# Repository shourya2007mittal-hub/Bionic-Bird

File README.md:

# Bionic-Bird

I made a bionic butterfly based on a custom ESP32 Board that holds an IMU and a Barometer for control. Is has 2 Servos each servos control a Wing. It uses a 3.7V battery and one can control it through your phone via bluetooth.

## Features

- Base on ESP32 Module
- Has IMU (MPU_6050)
- Has a Barometer (BMP280)
- Uses 2 High torque Servoes
- Would have LED strips on the wings

## Components BOM

| Item | Quantity | Price (USD) | Source |
|------|------------|------------|---------|
| PCBA | - | $129.29 | JLCPCB |
| PCB Shipping | - | $11.99 | JLCPCB |
| High Torque Servo | 2 | $22.04 (for 2) | https://robu.in/product/waveshare-2-3kg-dual-axis-serial-bus-servo/ |
| LED Strip | 1 | $3.82 | https://robu.in/product/5m-neon-light-dance-party-decor-light-neon-led-lamp-flexible-el-wire-rope-tube-waterproof-led-strip-only-el-wire-yellow/ |

## Cost Summary

| Item | Cost (USD) |
|------|------------|
| PCBA | $129.29 |
| PCB Shipping | $11.99 |
| High Torque Servo (2 units) | $22.04 |
| LED Strip | $3.82 |

**Total Estimated Cost:** **$167.14**

### Schematic

###  PCB Design

### 3D Design

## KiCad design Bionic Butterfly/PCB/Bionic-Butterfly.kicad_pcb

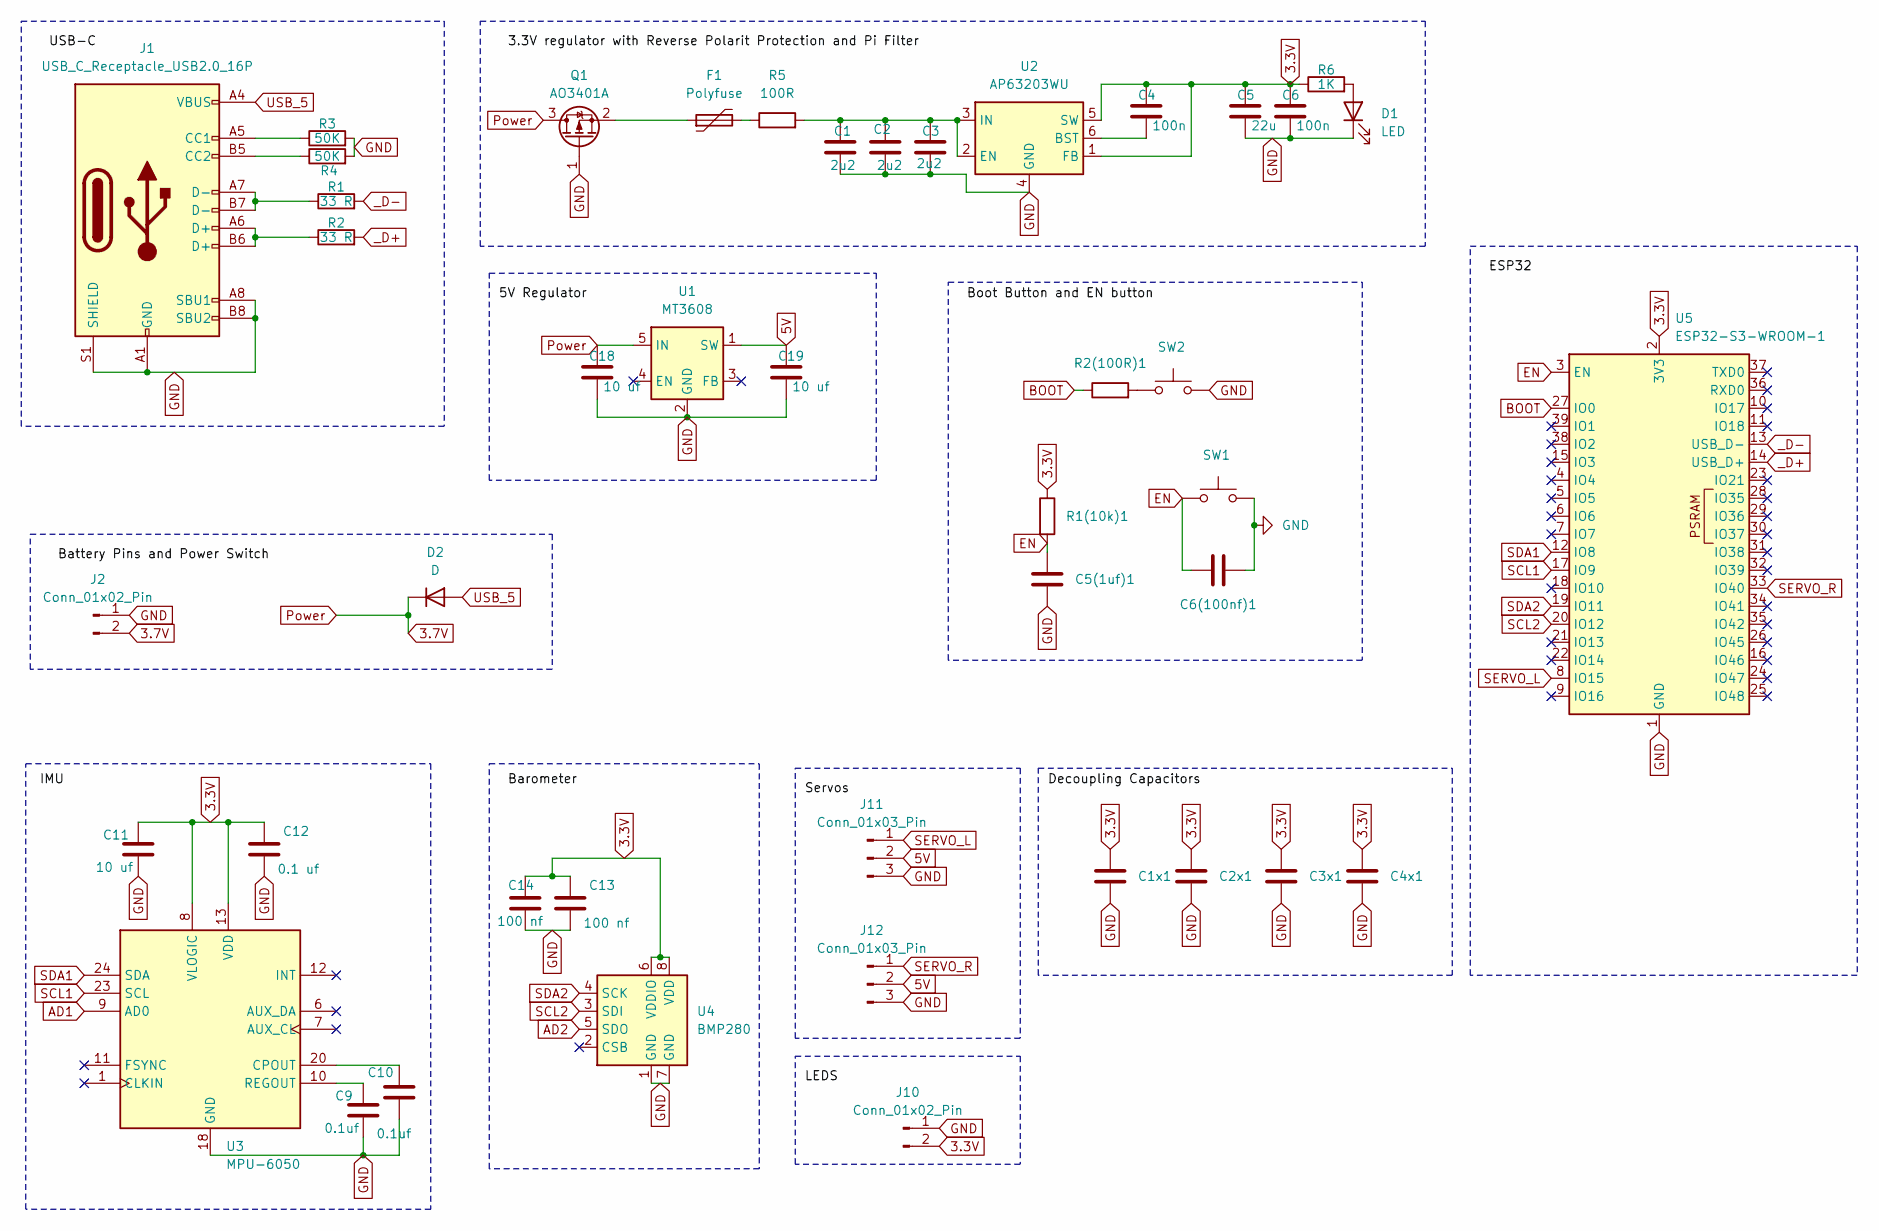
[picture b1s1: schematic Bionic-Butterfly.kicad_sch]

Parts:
C1, C2, C3: 2u2; C_0201_0603Metric
C1x1, C2x1, C3x1, C4x1, C5(1uf)1, C6(100nf)1: C; C_0805_2012Metric
C4, C6: 100n; C_0201_0603Metric
C5: 22u; C_0201_0603Metric
C9, C10: 0.1uf; C_0201_0603Metric
C11, C18, C19: 10 uf; C_0201_0603Metric
C12: 0.1 uf; C_0201_0603Metric
C13, C14: 100 nf; C_0201_0603Metric
D1: LED; LED_0201_0603Metric
D2: D; D_0201_0603Metric
F1: Polyfuse; C_0201_0603Metric
J1: USB_C_Receptacle_USB2.0_16P; USB_C_Receptacle_G-Switch_GT-USB-7010ASV
J2, J10: Conn_01x02_Pin; JST_EH_B2B-EH-A_1x02_P2.50mm_Vertical
J11, J12: Conn_01x03_Pin; JST_EH_B3B-EH-A_1x03_P2.50mm_Vertical
Q1: AO3401A; SOT-23
R1, R2: 33 R; R_0201_0603Metric_Pad0.64x0.40mm_HandSolder
R1(10k)1, R2(100R)1: R; R_0805_2012Metric
R3, R4: 50K; R_0201_0603Metric_Pad0.64x0.40mm_HandSolder
R5: 100R; R_0603_1608Metric
R6: 1K; R_0201_0603Metric_Pad0.64x0.40mm_HandSolder
SW1, SW2: SW_Push; SW_SPST_PTS810
U1: MT3608; SOT-23-6
U2: AP63203WU; TSOT-23-6
U3: MPU-6050; InvenSense_QFN-24_4x4mm_P0.5mm
U4: BMP280; Bosch_LGA-8_2x2.5mm_P0.65mm_ClockwisePinNumbering
U5: ESP32-S3-WROOM-1

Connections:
3.3V: C1x1.1, C2x1.1, C3x1.1, C4.1, C4x1.1, C5.1, C6.1, C11.1, C12.1, C13.1, C14.1, J10.2, R1(10k)1.1, R6.1, U2.1 (FB), U2.5 (SW), U3.8 (VLOGIC), U3.13 (VDD), U4.6 (VDDIO), U4.8 (VDD), U5.2 (3V3)
3.7V: C18.1, D2.1 (K), J2.2, Q1.3 (D), U1.5 (IN)
5V: C19.1, J11.2, J12.2, U1.1 (SW)
AD1: U3.9 (AD0)
AD2: U4.5 (SDO)
BOOT: R2(100R)1.1, U5.27 (IO0)
EN: C5(1uf)1.1, C6(100nf)1.1, R1(10k)1.2, SW1.1, U5.3 (EN)
GND: C1.2, C1x1.2, C2.2, C2x1.2, C3.2, C3x1.2, C4x1.2, C5.2, C5(1uf)1.2, C6.2, C6(100nf)1.2, C9.2, C10.2, C11.2, C12.2, C13.2, C14.2, C18.2, C19.2, D1.1 (K), J1.A1 (GND), J1.A8 (SBU1), J1.A12 (GND), J1.B1 (GND), J1.B8 (SBU2), J1.B12 (GND), J1.S1 (SHIELD), J2.1, J10.1, J11.3, J12.3, Q1.1 (G), R3.2, R4.2, SW1.2, SW2.2, U1.2 (GND), U2.4 (GND), U3.18 (GND), U4.1 (GND), U4.7 (GND), U5.1 (GND), U5.40 (GND), U5.41 (GND)
unnamed: D1.2 (A), R6.2
unnamed: F1.2, R5.1
unnamed: J1.A5 (CC1), R3.1
unnamed: J1.B5 (CC2), R4.1
unnamed: J1.A6 (D+), J1.B6 (D+), R2.1
unnamed: J1.A7 (D-), J1.B7 (D-), R1.1
unnamed: F1.1, Q1.2 (S)
unnamed: R2(100R)1.2, SW2.1
unnamed: C4.2, U2.6 (BST)
unnamed: C1.1, C2.1, C3.1, R5.2, U2.2 (EN), U2.3 (IN)
unnamed: C10.1, U3.20 (CPOUT)
unnamed: C9.1, U3.10 (REGOUT)
SCL1: U3.23 (SCL), U5.17 (IO9)
SCL2: U4.3 (SDI), U5.20 (IO12)
SDA1: U3.24 (SDA), U5.12 (IO8)
SDA2: U4.4 (SCK), U5.19 (IO11)
SERVO_L: J11.1, U5.8 (IO15)
SERVO_R: J12.1, U5.33 (IO40)
USB_5: D2.2 (A), J1.A4 (VBUS), J1.A9 (VBUS), J1.B4 (VBUS), J1.B9 (VBUS)
_D+: R2.2, U5.14 (USB_D+)
_D-: R1.2, U5.13 (USB_D-)

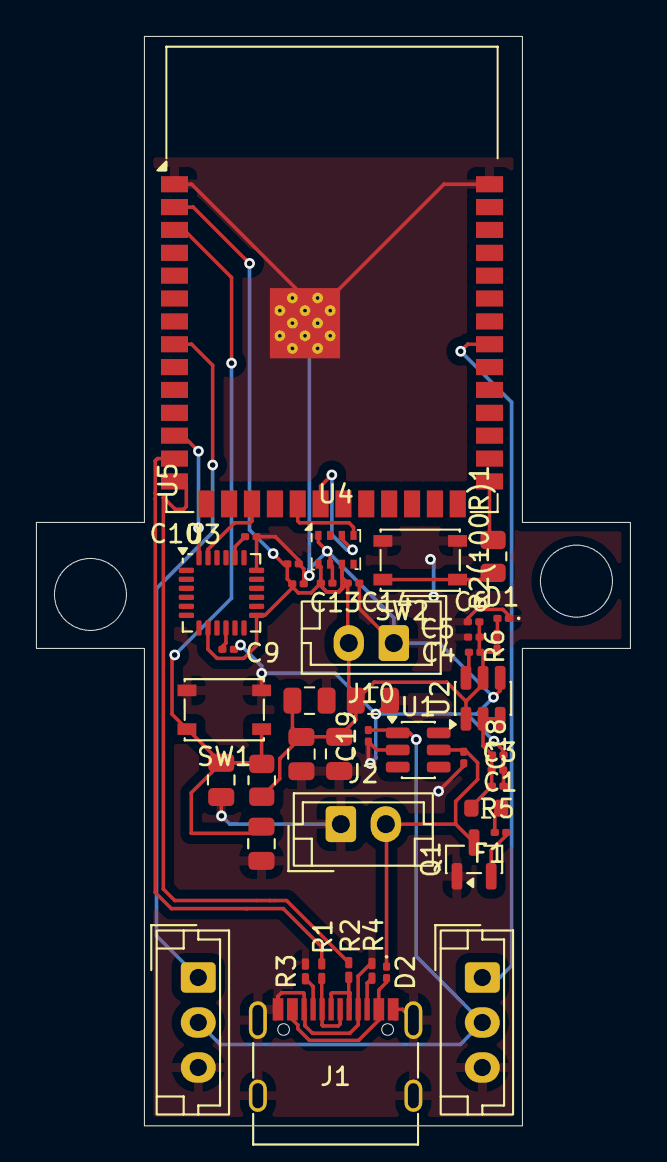
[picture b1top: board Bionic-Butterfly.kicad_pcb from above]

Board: 2 copper layers, 33.0 x 60.5 mm, 44 parts (0 on the bottom side), 27 nets.
